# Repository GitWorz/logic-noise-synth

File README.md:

# Logic Noise Synth — "Circuits son"

Polyphonic logic-gate synthesizer built during the **Logic Noise Workshop** (ESILV, Circuits course).
Square-wave oscillators made from a **74HC14** Schmitt-trigger hex inverter are sequenced by a **74HC595** shift register, mixed, amplified and played through a speaker/piezo.

**Team:** Pierre — *(add teammates)*

| Stage | Tool | Files |
|---|---|---|
| 1. Breadboard prototypes (step by step) | Breadboard + oscilloscope | [`media/photos`](media/photos), [`media/video`](media/video), [`media/audio`](media/audio), [`media/scope`](media/scope) |
| 2. Hand-drawn circuits | Paper | [`media/hand-drawn`](media/hand-drawn) |
| 3. Breadboard diagram + generated schematic | Tinkercad | [`media/tinkercad`](media/tinkercad) |
| 4. Soldered synth (V1) | Perfboard + soldering iron | [`media/photos`](media/photos) |
| 5. PCB version 2 | KiCad | [`kicad/`](kicad) |

---

## Table of contents

1. [How it works](#1-how-it-works)
2. [Reference circuit](#2-reference-circuit)
3. [Breadboard prototypes](#3-breadboard-prototypes)
4. [Hand-drawn circuits & oscilloscope captures](#4-hand-drawn-circuits--oscilloscope-captures)
5. [Tinkercad breadboard diagram & schematic](#5-tinkercad-breadboard-diagram--schematic)
6. [Soldered synth (V1)](#6-soldered-synth-v1)
7. [KiCad V2 — PCB with new functionality](#7-kicad-v2--pcb-with-new-functionality)
8. [Bill of materials](#8-bill-of-materials)
9. [Repository structure](#9-repository-structure)
10. [References](#10-references)

---

## 1. How it works

### 1.1 The Schmitt-trigger oscillator

An inverter outputs the opposite of its input. Feed the output back to the input through a resistor **R** and add a capacitor **C** to ground: the capacitor charges and discharges through R, and each time its voltage crosses one of the two Schmitt thresholds the output flips. The result is a square wave at the output (and a triangle-like ramp on the capacitor).

```
           R (10 kΩ pot)
     ┌────/\/\/\────┐
     │              │
 in ─┴──|>o─────────┴── out  (square wave)
     │  74HC14
     C
     │
    GND
```

Frequency (workshop rule of thumb):

$$f \approx \frac{k}{RC}, \qquad 0.2 < k < 1.0$$

Turning the potentiometer changes R, so it changes the pitch. Changing C changes the range: µF values give rhythm (a few Hz), 100 nF and below give audible tones.

### 1.2 Sequencing with the 74HC595

Two more oscillators act as a **CLOCK** and a **DATA** source:

- **CLOCK** → `SRCLK` and `RCLK`: on each tick the register shifts one position.
- **DATA** → `SER`: the bit pushed in on each tick is 1 or 0 depending on the DATA oscillator's state at that moment.

Because the two oscillators run at unrelated rates, the bit pattern moving through `QA…QH` is quasi-random and evolves constantly. Outputs of the register gate the pitch oscillators through diodes (reference circuit) or drive LEDs (our V2): this turns 3 free-running tones into a rhythmic, generative pattern.

### 1.3 Mixing and amplifying

The oscillator outputs are summed through equal resistors (passive mixer), AC-coupled through an electrolytic capacitor to remove the DC offset, then amplified (LM386 in the reference circuit) to drive a speaker.

---

## 2. Reference circuit

Final target circuit given by the workshop (correction):

| Block | Gate | R | C | Approx. range* | Role |
|---|---|---|---|---|---|
| Pitch A | 74HC14 | 10 kΩ pot | 1 µF | 20 – 100 Hz and up | Bass tone |
| Pitch B | 74HC14 | 10 kΩ pot | 10 µF | 2 – 10 Hz and up | Slow pulse |
| Pitch C | 74HC14 | 10 kΩ pot | 0.1 µF | 200 – 1000 Hz and up | High tone |
| Clock osc | 74HC14 | 10 kΩ pot | 10 µF | 2 – 10 Hz and up | Shift-register clock + clock LED |
| Data osc | 74HC14 | 10 kΩ pot | 10 µF | 2 – 10 Hz and up | Shift-register serial data |
| Mixer | — | 3 × 100 Ω | — | — | Sums Pitch A/B/C |
| Amplifier | LM386 | — | 100 µF in / 220 µF out | — | Drives the speaker |

\* Computed with *f = k/RC*, R = 10 kΩ (pot at maximum), k between 0.2 and 1. Lowering the pot raises the frequency.

Shift-register wiring: `QB → Pitch C`, `QE → Pitch B`, `QH → Pitch A` (through diodes), `OE` to GND, `SRCLR` to 5 V.

---

## 3. Breadboard prototypes

The circuit was built incrementally, following the workshop steps:

1. Single 74HC14 oscillator blinking an LED (10 µF, 1 kΩ).
2. Potentiometer in the feedback loop → variable rate.
3. Smaller capacitor → audible tone, observed on the oscilloscope.
4. Amplifier stage → sound out of the speaker/piezo.
5. Several oscillators mixed through resistors.
6. 74HC595 shift register clocked by a CLOCK oscillator and fed by a DATA oscillator, LEDs on its outputs.

### Full prototype on two breadboards

| Bench view | Top view (running, LEDs lit) |
|---|---|
|  |  |

Left board: 74HC14 oscillators, op-amp, potentiometers and capacitors. Right board: 74HC595 shift register and its LED display. Power (5 V / GND) is taken from an Arduino board.

### Videos / GIFs

<!-- Drop the files in media/video and uncomment/adapt the lines below.
     GitHub plays .mp4 files dragged into the README editor; GIFs display inline. -->

| Circuit | Media |
|---|---|
| Single oscillator + LED | `media/video/01_oscillator_led.gif` *(to add)* |
| Pitch control with the potentiometer | `media/video/02_pitch_pot.mp4` *(to add)* |
| Shift-register sequence (LEDs) | `media/video/03_shift_register.mp4` *(to add)* |
| Full synth playing | `media/video/04_full_synth.mp4` *(to add)* |

### Audio recordings

| Recording | File |
|---|---|
| Single oscillator, pot sweep | `media/audio/01_single_osc_sweep.mp3` *(to add)* |
| Two oscillators mixed | `media/audio/02_mix.mp3` *(to add)* |
| Full sequenced synth | `media/audio/03_full_synth.mp3` *(to add)* |

---

## 4. Hand-drawn circuits & oscilloscope captures

### Hand-drawn schematics

| Drawing | File |
|---|---|
| Schmitt-trigger oscillator | `media/hand-drawn/oscillator.jpg` *(to add)* |
| Full synth | `media/hand-drawn/full_synth.jpg` *(to add)* |

### Oscilloscope screenshots

| Signal | What to observe | File |
|---|---|---|
| Oscillator output (74HC14 out) | Square wave 0 V → Vcc; period changes with the pot | `media/scope/osc_output.png` *(to add)* |
| Capacitor node (74HC14 in) | Ramp between the two Schmitt thresholds | `media/scope/osc_capacitor.png` *(to add)* |
| Mixer output | Stepped sum of several square waves | `media/scope/mix.png` *(to add)* |
| CLOCK vs 595 output | Output changes only on clock edges | `media/scope/clock_vs_q.png` *(to add)* |

Scope settings used: probe ground clip on circuit GND, ~1 V/div, ~200 ms/div for slow oscillators, µs–ms/div for audio-rate ones.

---

## 5. Tinkercad breadboard diagram & schematic

### Breadboard diagram

### Schematic generated by Tinkercad

| Sheet 1 | Sheet 2 |
|---|---|
|  |  |

PDF: [`media/tinkercad/tinkercad_schematic.pdf`](media/tinkercad/tinkercad_schematic.pdf)

Differences from the reference circuit:

| Reference | Tinkercad version | Reason |
|---|---|---|
| LM386 audio amplifier | 741 op-amp (U2) | Part available in Tinkercad |
| Speaker | Piezo buzzer | Part available in Tinkercad |
| 5 V bench supply | Arduino Uno 5 V / 3.3 V / GND | Power source only, no code |
| QB/QE/QH gate the pitch oscillators | 595 outputs drive 7 LEDs | Visual feedback of the sequence |
| — | LEDs on oscillator outputs | Visual feedback of each oscillator |

---

## 6. Soldered synth (V1)

The breadboard circuit was transferred onto a 2.54 mm perfboard: 74HC14 oscillators, 74HC595 shift register with its LED row, 8-pin audio amplifier, two front-panel potentiometers and a speaker on a twisted pair. Connections are made point-to-point with wire on the solder side.

| Top (components) | Solder side | With speaker |
|---|---|---|
|  |  |  |

| Proof of functioning | File |
|---|---|
| Video with sound | `media/video/v1_soldered_working.mp4` *(to add)* |

---

## 7. KiCad V2 — PCB with new functionality

Files: [`kicad/circuits_son.kicad_sch`](kicad/circuits_son.kicad_sch), [`kicad/circuits_son.kicad_pcb`](kicad/circuits_son.kicad_pcb), project [`kicad/circuits_son.kicad_pro`](kicad/circuits_son.kicad_pro). Open the `.kicad_pro` in KiCad.

| PCB layout (KiCad) | 3D view (KiCad) |
|---|---|
|  |  |

### Board specifications

| Parameter | Value |
|---|---|
| Size | 100 × 100 mm |
| Layers | 2 (F.Cu / B.Cu), 1.6 mm FR-4 |
| Copper pours | GND on both layers |
| Track width | 0.4 mm (Default net class), clearance 0.25 mm |
| Components | All through-hole (DIP-8, DIP-14, DIP-16, 5 mm LEDs, radial caps, RM-065 vertical potentiometers) |
| Mounting | 4 × M3 holes (H1–H4) |
| Power input | J1, 2-pin 2.54 mm header (3.3 V / GND) |

### What V2 adds compared with the soldered V1

1. **LED sequencer display**: 7 LEDs (D3–D9: red, green, blue, yellow) on the 74HC595 outputs `Q0–Q6` show the bit pattern shifting in real time, so the rhythm the circuit generates can be seen as well as heard.
2. **Per-oscillator activity LEDs**: D1, D2, D10, D11 on the outputs of the four 74HC14 oscillators (pitch 1, DATA, pitch 2, CLOCK) give a visual tempo for each one.
3. **Standalone board**: the Arduino used only as a power supply is replaced by J1 (3.3 V / GND), and the board has mounting holes so it can be put in an enclosure.

### Corrections made while converting Tinkercad → KiCad

| Issue in the Tinkercad version | Correction in KiCad |
|---|---|
| LEDs connected without current-limiting resistors | R4–R14 in series with each LED (220 Ω, 47 Ω for the blue LEDs) |
| Op-amp U2 pinout wrong | V+ on pin 7, output on pin 6 |
| Unused 74HC14 inputs floating | 1A and 2A tied to GND |
| No supply decoupling | C8, C9 = 100 nF next to U3 and U4 |
| Arduino on the board | Replaced by connector J1 |

### Netlist summary (from the PCB)

| Block | Parts | Nets |
|---|---|---|
| Oscillator 1 (74HC14 gate 3, pins 5→6) | RPOT4, C2 33 µF | `OSC3_A`, `OSC3_Y` → LED D1 |
| Oscillator 2 (gate 4, pins 9→8) | RPOT5, C6 22 µF | `OSC4_A`, `OSC4_Y` → LED D10 |
| DATA oscillator (gate 5, pins 11→10) | RPOT3, C3 22 µF | `SER` → 74HC595 pin 14, LED D2 |
| CLOCK oscillator (gate 6, pins 13→12) | RPOT2, C7 22 µF | `CLK` → 74HC595 SRCLK + RCLK, LED D11 |
| Mixer | R1, R2, R3 = 1 kΩ | `MIX` |
| Amplifier | U2 741, C5 220 µF in, C4 220 µF out | `AMP_IN`, `AMP_OUT`, `BUZ` → PIEZO1 |
| Shift register | U4 74HC595, `OE` to GND, `SRCLR` to 3.3 V | `Q0–Q6` → D5, D6, D8, D4, D9, D7, D3 |

---

## 8. Bill of materials

KiCad V2 (from the schematic):

| Ref | Qty | Value | Footprint |
|---|---|---|---|
| U3 | 1 | 74HC14 hex Schmitt inverter | DIP-14 |
| U4 | 1 | 74HC595 8-bit shift register | DIP-16 |
| U2 | 1 | 741 op-amp | DIP-8 |
| RPOT2–RPOT5 | 4 | 10 kΩ potentiometer | RM-065 vertical (project footprint `circuits_son:Potentiometre_RM-065_Vertical`) |
| C2 | 1 | 33 µF electrolytic | Radial D5 mm |
| C3, C6, C7 | 3 | 22 µF electrolytic | Radial D5 mm |
| C4, C5 | 2 | 220 µF electrolytic | Radial D6.3 mm |
| C8, C9 | 2 | 100 nF ceramic | Disc 5 mm |
| R1–R3 | 3 | 1 kΩ | Axial DIN0207 |
| R4–R8, R10, R11, R13, R14 | 9 | 220 Ω | Axial DIN0207 |
| R9, R12 | 2 | 47 Ω | Axial DIN0207 |
| D1, D2, D7, D8, D10, D11 | 6 | Yellow LED 5 mm | LED_D5.0mm |
| D3, D4 | 2 | Red LED 5 mm | LED_D5.0mm |
| D5 | 1 | Green LED 5 mm | LED_D5.0mm |
| D6, D9 | 2 | Blue LED 5 mm | LED_D5.0mm |
| PIEZO1 | 1 | Piezo buzzer | 12 × 9.5 mm, 7.6 mm pitch |
| J1 | 1 | 2-pin header 3.3 V / GND | 1×02, 2.54 mm |
| H1–H4 | 4 | M3 mounting hole | 3.2 mm |

Tinkercad component list: [`bom/Composants_tinkercad.csv`](bom/Composants_tinkercad.csv).

---

## 9. Repository structure

```
.
├── README.md
├── bom/
│   └── Composants_tinkercad.csv        # Tinkercad parts list
├── docs/
│   └── BOOTCAMP_WORKSHOP_2024.pdf      # Workshop handout (Logic Noise)
├── kicad/                              # V2: schematic + PCB
│   ├── circuits_son.kicad_pro
│   ├── circuits_son.kicad_prl
│   ├── circuits_son.kicad_sch
│   ├── circuits_son.kicad_pcb
│   └── fp-lib-table                    # project footprint library
└── media/
    ├── audio/                          # Recordings
    ├── hand-drawn/                     # Paper schematics
    ├── kicad/                          # PCB layout + 3D view
    ├── photos/                         # Breadboard + soldered board
    ├── reference/                      # Reference schematic (FINAL)
    ├── scope/                          # Oscilloscope screenshots
    ├── tinkercad/                      # Breadboard diagram + schematic
    └── video/                          # Videos / GIFs
```

---

## 10. References

- Workshop handout: [`docs/BOOTCAMP_WORKSHOP_2024.pdf`](docs/BOOTCAMP_WORKSHOP_2024.pdf)
- Elliot Williams, *Logic Noise* series — Hackaday: https://hackaday.com/series_of_posts/logic-noise/
- *Exactly How Schmitt Trigger Oscillators Work* — All About Circuits: https://www.allaboutcircuits.com/technical-articles/exactly-how-schmitt-trigger-oscillators-work/
- Nicolas Collins, *Handmade Electronic Music: The Art of Hardware Hacking*
- Datasheets: 74HC14, 74HC595, LM386, µA741 (Texas Instruments)

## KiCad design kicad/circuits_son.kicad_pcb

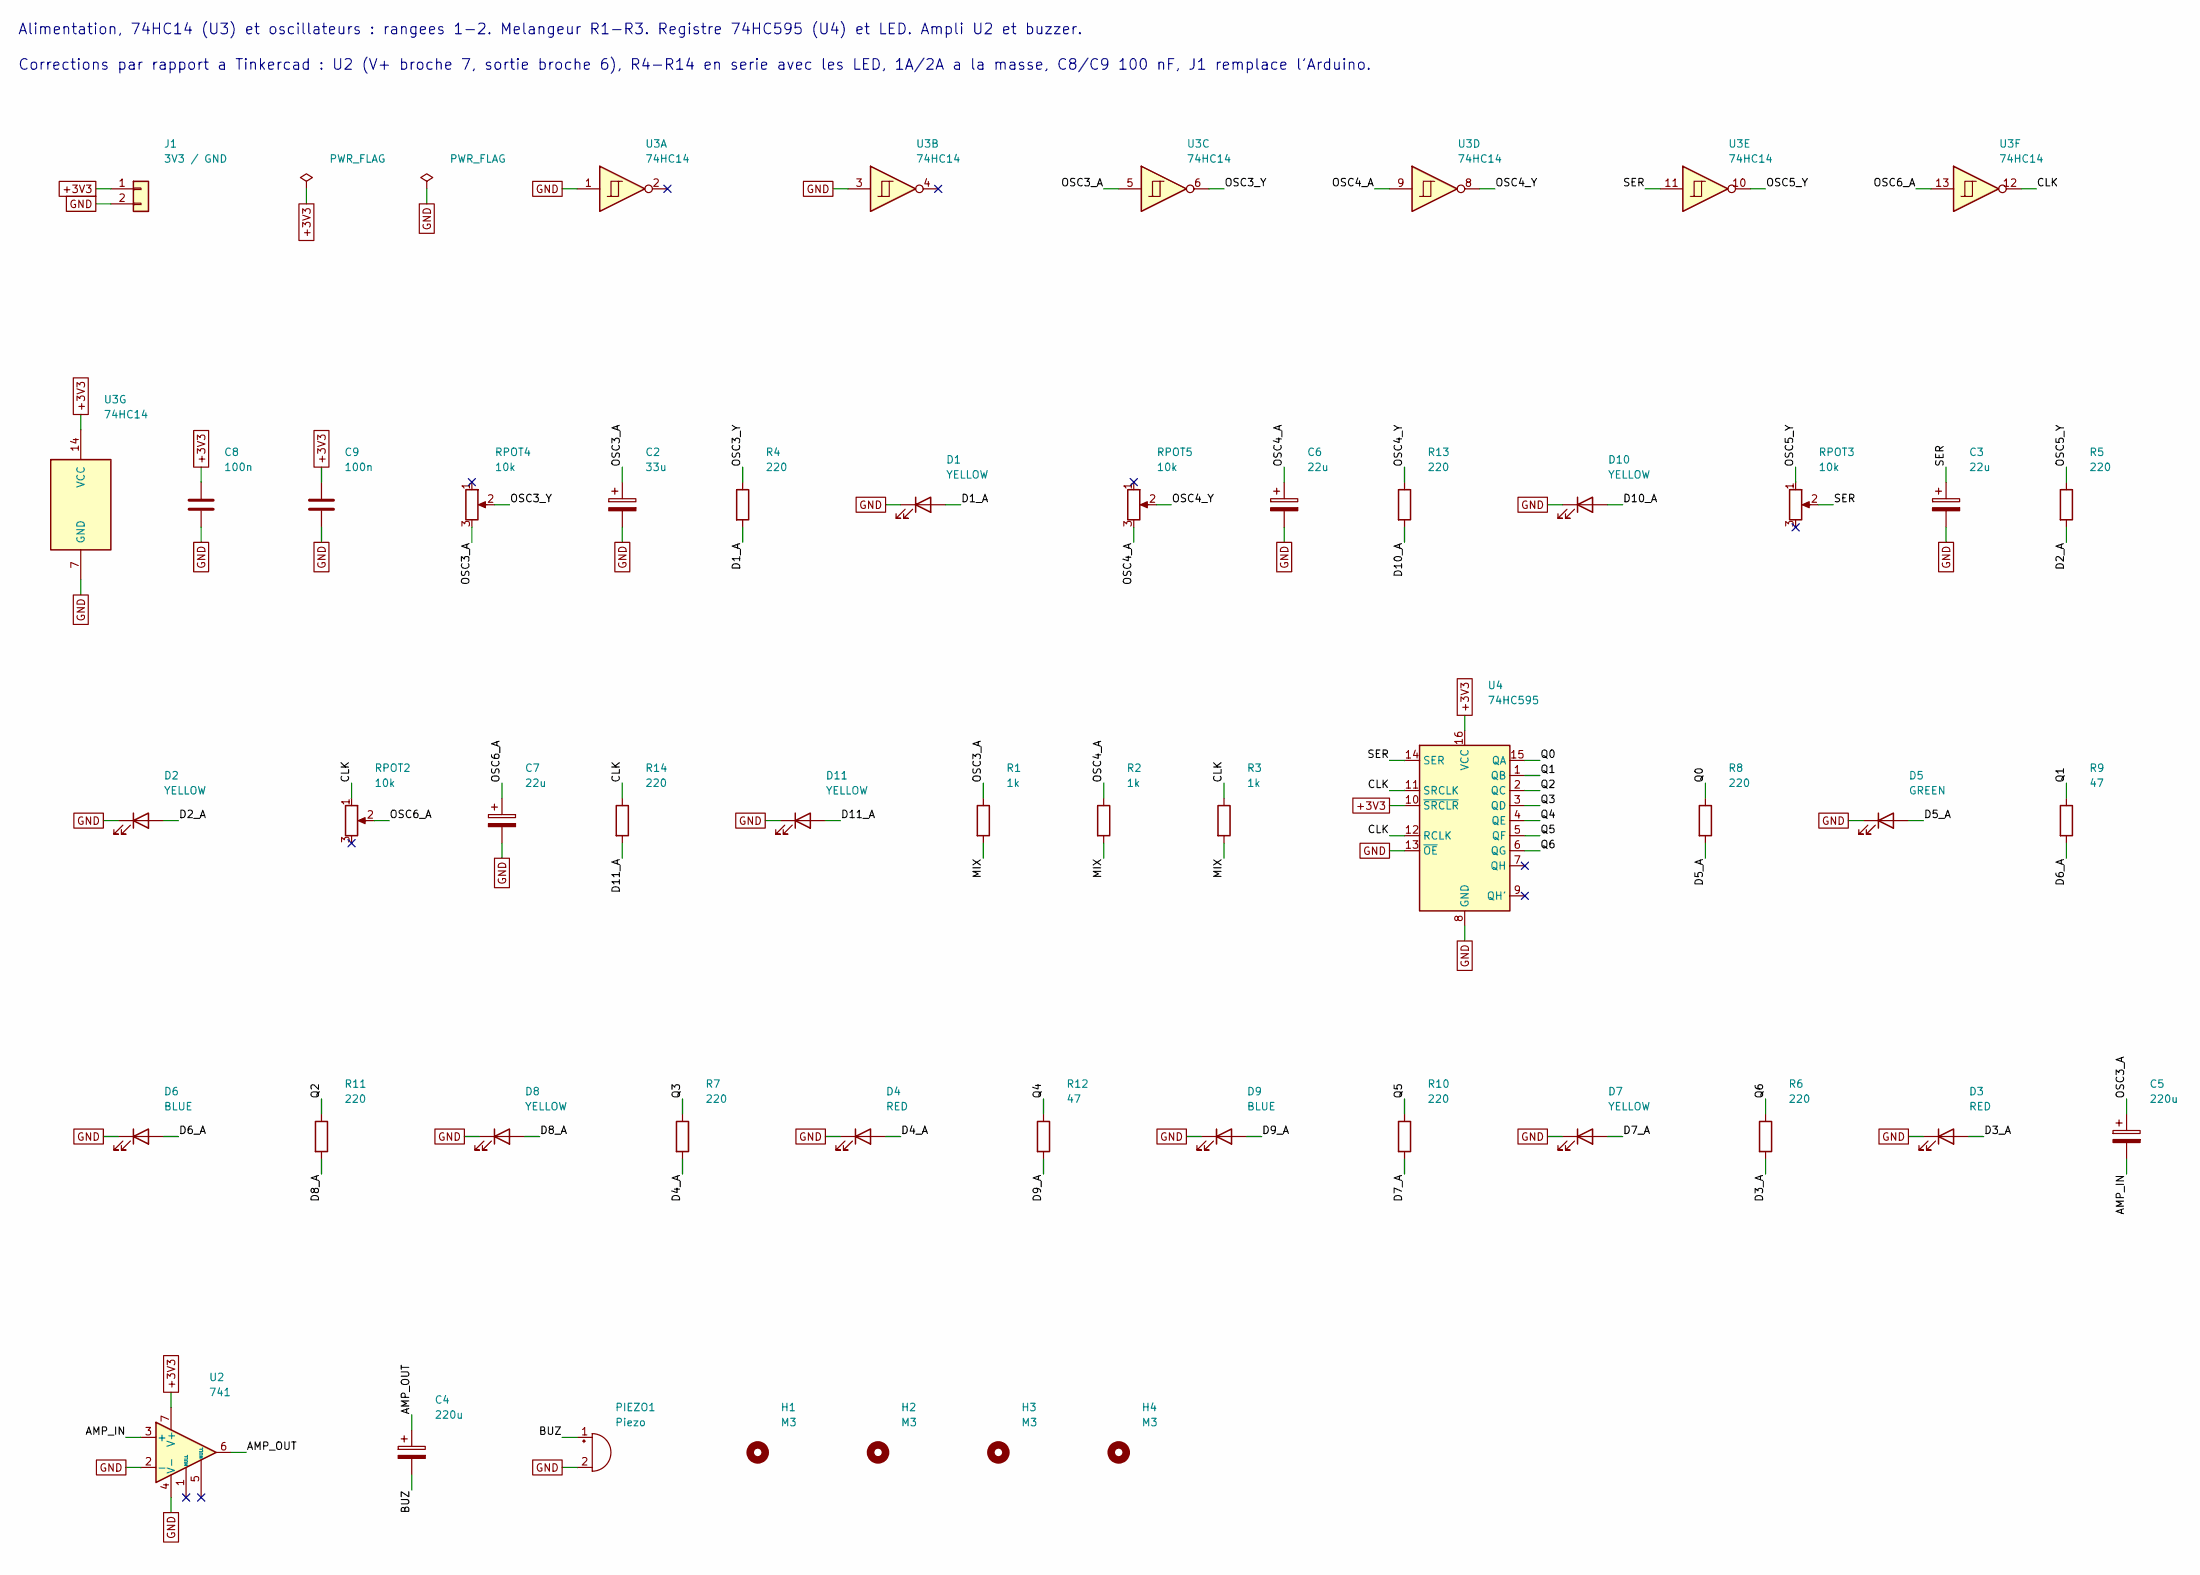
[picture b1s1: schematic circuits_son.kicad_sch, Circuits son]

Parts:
C2: 33u; CP_Radial_D5.0mm_P2.50mm
C3, C6, C7: 22u; CP_Radial_D5.0mm_P2.50mm
C4, C5: 220u; CP_Radial_D6.3mm_P2.50mm
C8, C9: 100n; C_Disc_D5.0mm_W2.5mm_P5.00mm
D1, D2, D7, D8, D10, D11: YELLOW; LED_D5.0mm
D3, D4: RED; LED_D5.0mm
D5: GREEN; LED_D5.0mm
D6, D9: BLUE; LED_D5.0mm
H1, H2, H3, H4: M3; MountingHole_3.2mm_M3
J1: 3V3 / GND; PinHeader_1x02_P2.54mm_Vertical
PIEZO1: Piezo; Buzzer_12x9.5RM7.6
R1, R2, R3: 1k; R_Axial_DIN0207_L6.3mm_D2.5mm_P10.16mm_Horizontal
R4, R5, R6, R7, R8, R10, R11, R13, R14: 220; R_Axial_DIN0207_L6.3mm_D2.5mm_P10.16mm_Horizontal
R9, R12: 47; R_Axial_DIN0207_L6.3mm_D2.5mm_P10.16mm_Horizontal
RPOT2, RPOT3, RPOT4, RPOT5: 10k; Potentiometre_RM-065_Vertical
U2: 741; DIP-8_W7.62mm
U3: 74HC14; DIP-14_W7.62mm
U4: 74HC595; DIP-16_W7.62mm

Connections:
+3V3: C8.1, C9.1, J1.1, U2.7 (V+), U3.14 (VCC), U4.10 (~SRCLR), U4.16 (VCC)
/AMP_IN: C5.2, U2.3 (+)
/AMP_OUT: C4.1, U2.6
/BUZ: C4.2, PIEZO1.1 (+)
/CLK: R3.1, R14.1, RPOT2.1, U3.12, U4.11 (SRCLK), U4.12 (RCLK)
/D1_A: D1.2 (A), R4.2
/D2_A: D2.2 (A), R5.2
/D3_A: D3.2 (A), R6.2
/D4_A: D4.2 (A), R7.2
/D5_A: D5.2 (A), R8.2
/D6_A: D6.2 (A), R9.2
/D7_A: D7.2 (A), R10.2
/D8_A: D8.2 (A), R11.2
/D9_A: D9.2 (A), R12.2
/D10_A: D10.2 (A), R13.2
/D11_A: D11.2 (A), R14.2
/MIX: R1.2, R2.2, R3.2
/OSC3_A: C2.1, C5.1, R1.1, RPOT4.3, U3.5
/OSC3_Y: R4.1, RPOT4.2, U3.6
/OSC4_A: C6.1, R2.1, RPOT5.3, U3.9
/OSC4_Y: R13.1, RPOT5.2, U3.8
/OSC5_Y: R5.1, RPOT3.1, U3.10
/OSC6_A: C7.1, RPOT2.2, U3.13
/Q0: R8.1, U4.15 (QA)
/Q1: R9.1, U4.1 (QB)
/Q2: R11.1, U4.2 (QC)
/Q3: R7.1, U4.3 (QD)
/Q4: R12.1, U4.4 (QE)
/Q5: R10.1, U4.5 (QF)
/Q6: R6.1, U4.6 (QG)
/SER: C3.1, RPOT3.2, U3.11, U4.14 (SER)
GND: C2.2, C3.2, C6.2, C7.2, C8.2, C9.2, D1.1 (K), D2.1 (K), D3.1 (K), D4.1 (K), D5.1 (K), D6.1 (K), D7.1 (K), D8.1 (K), D9.1 (K), D10.1 (K), D11.1 (K), J1.2, PIEZO1.2 (-), U2.2 (-), U2.4 (V-), U3.1, U3.3, U3.7 (GND), U4.8 (GND), U4.13 (~OE)

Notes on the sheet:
Alimentation, 74HC14 (U3) et oscillateurs : rangees 1-2. Melangeur R1-R3. Registre 74HC595 (U4) et LED. Ampli U2 et buzzer.
Corrections par rapport a Tinkercad : U2 (V+ broche 7, sortie broche 6), R4-R14 en serie avec les LED, 1A/2A a la masse, C8/C9 100 nF, J1 remplace l'Arduino.

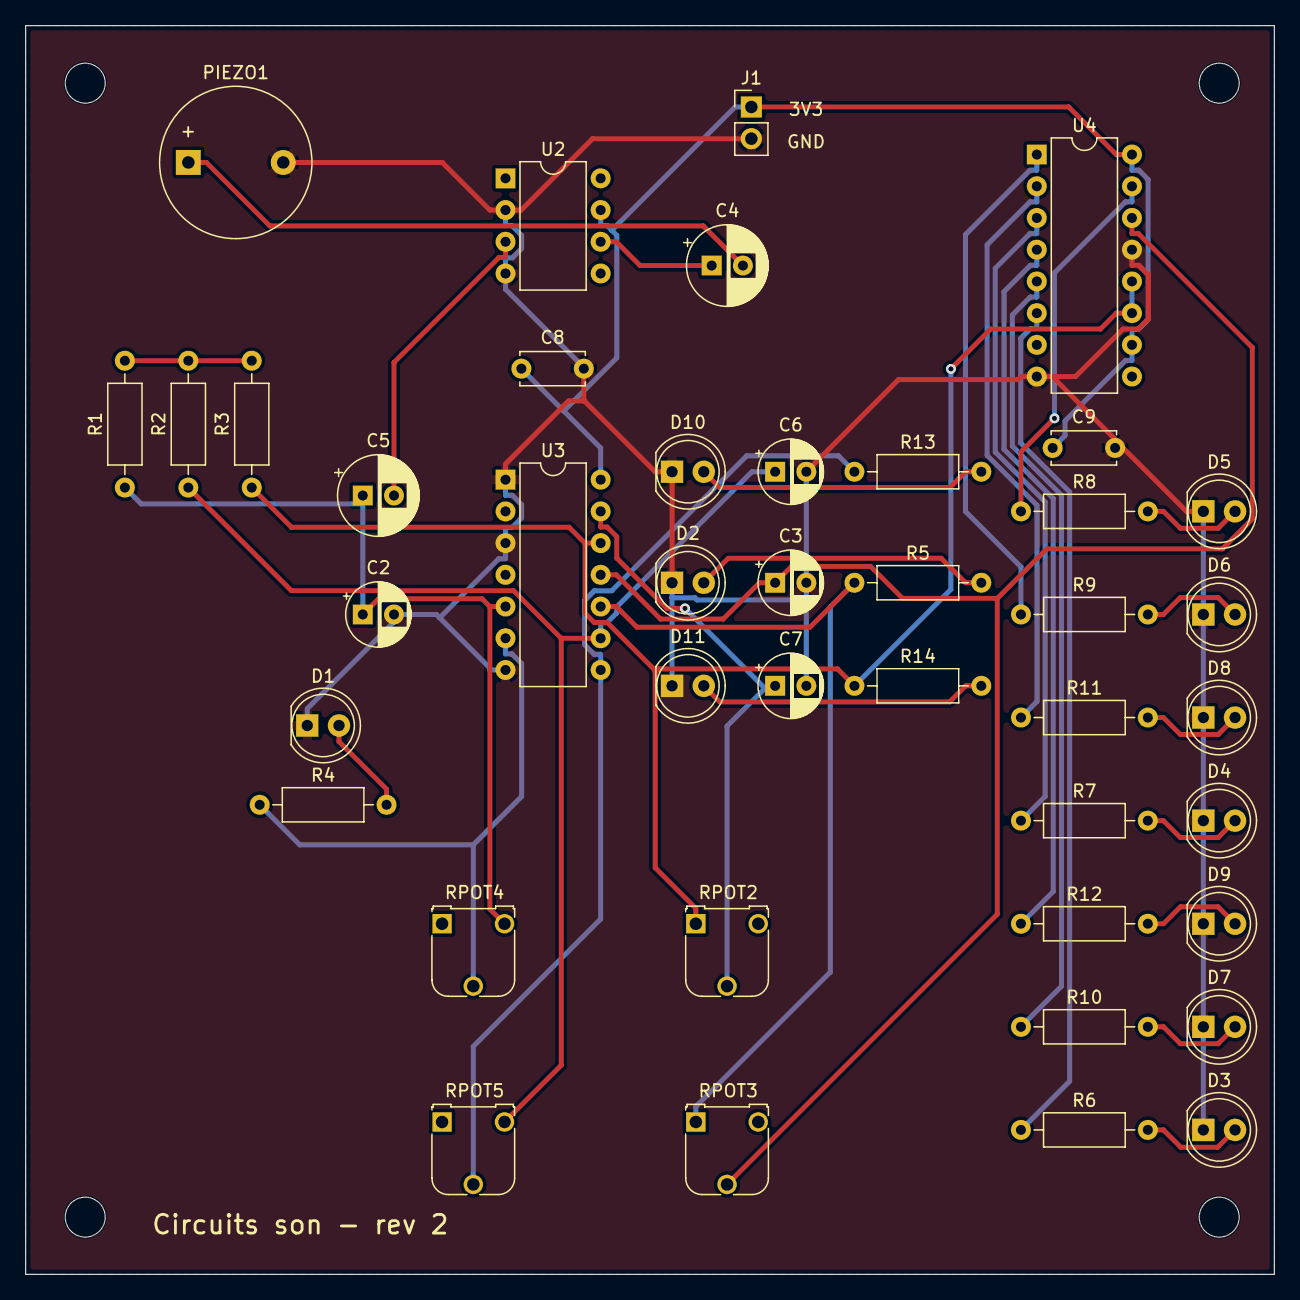
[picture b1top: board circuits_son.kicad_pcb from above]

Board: 2 copper layers, 100.0 x 100.0 mm, 46 parts (0 on the bottom side), 32 nets.
